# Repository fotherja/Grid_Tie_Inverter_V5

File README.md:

# Grid_Tie_Inverter_V5

Please refer to my site ( www.jamesfotherby.com ) where this project is being documented in detail

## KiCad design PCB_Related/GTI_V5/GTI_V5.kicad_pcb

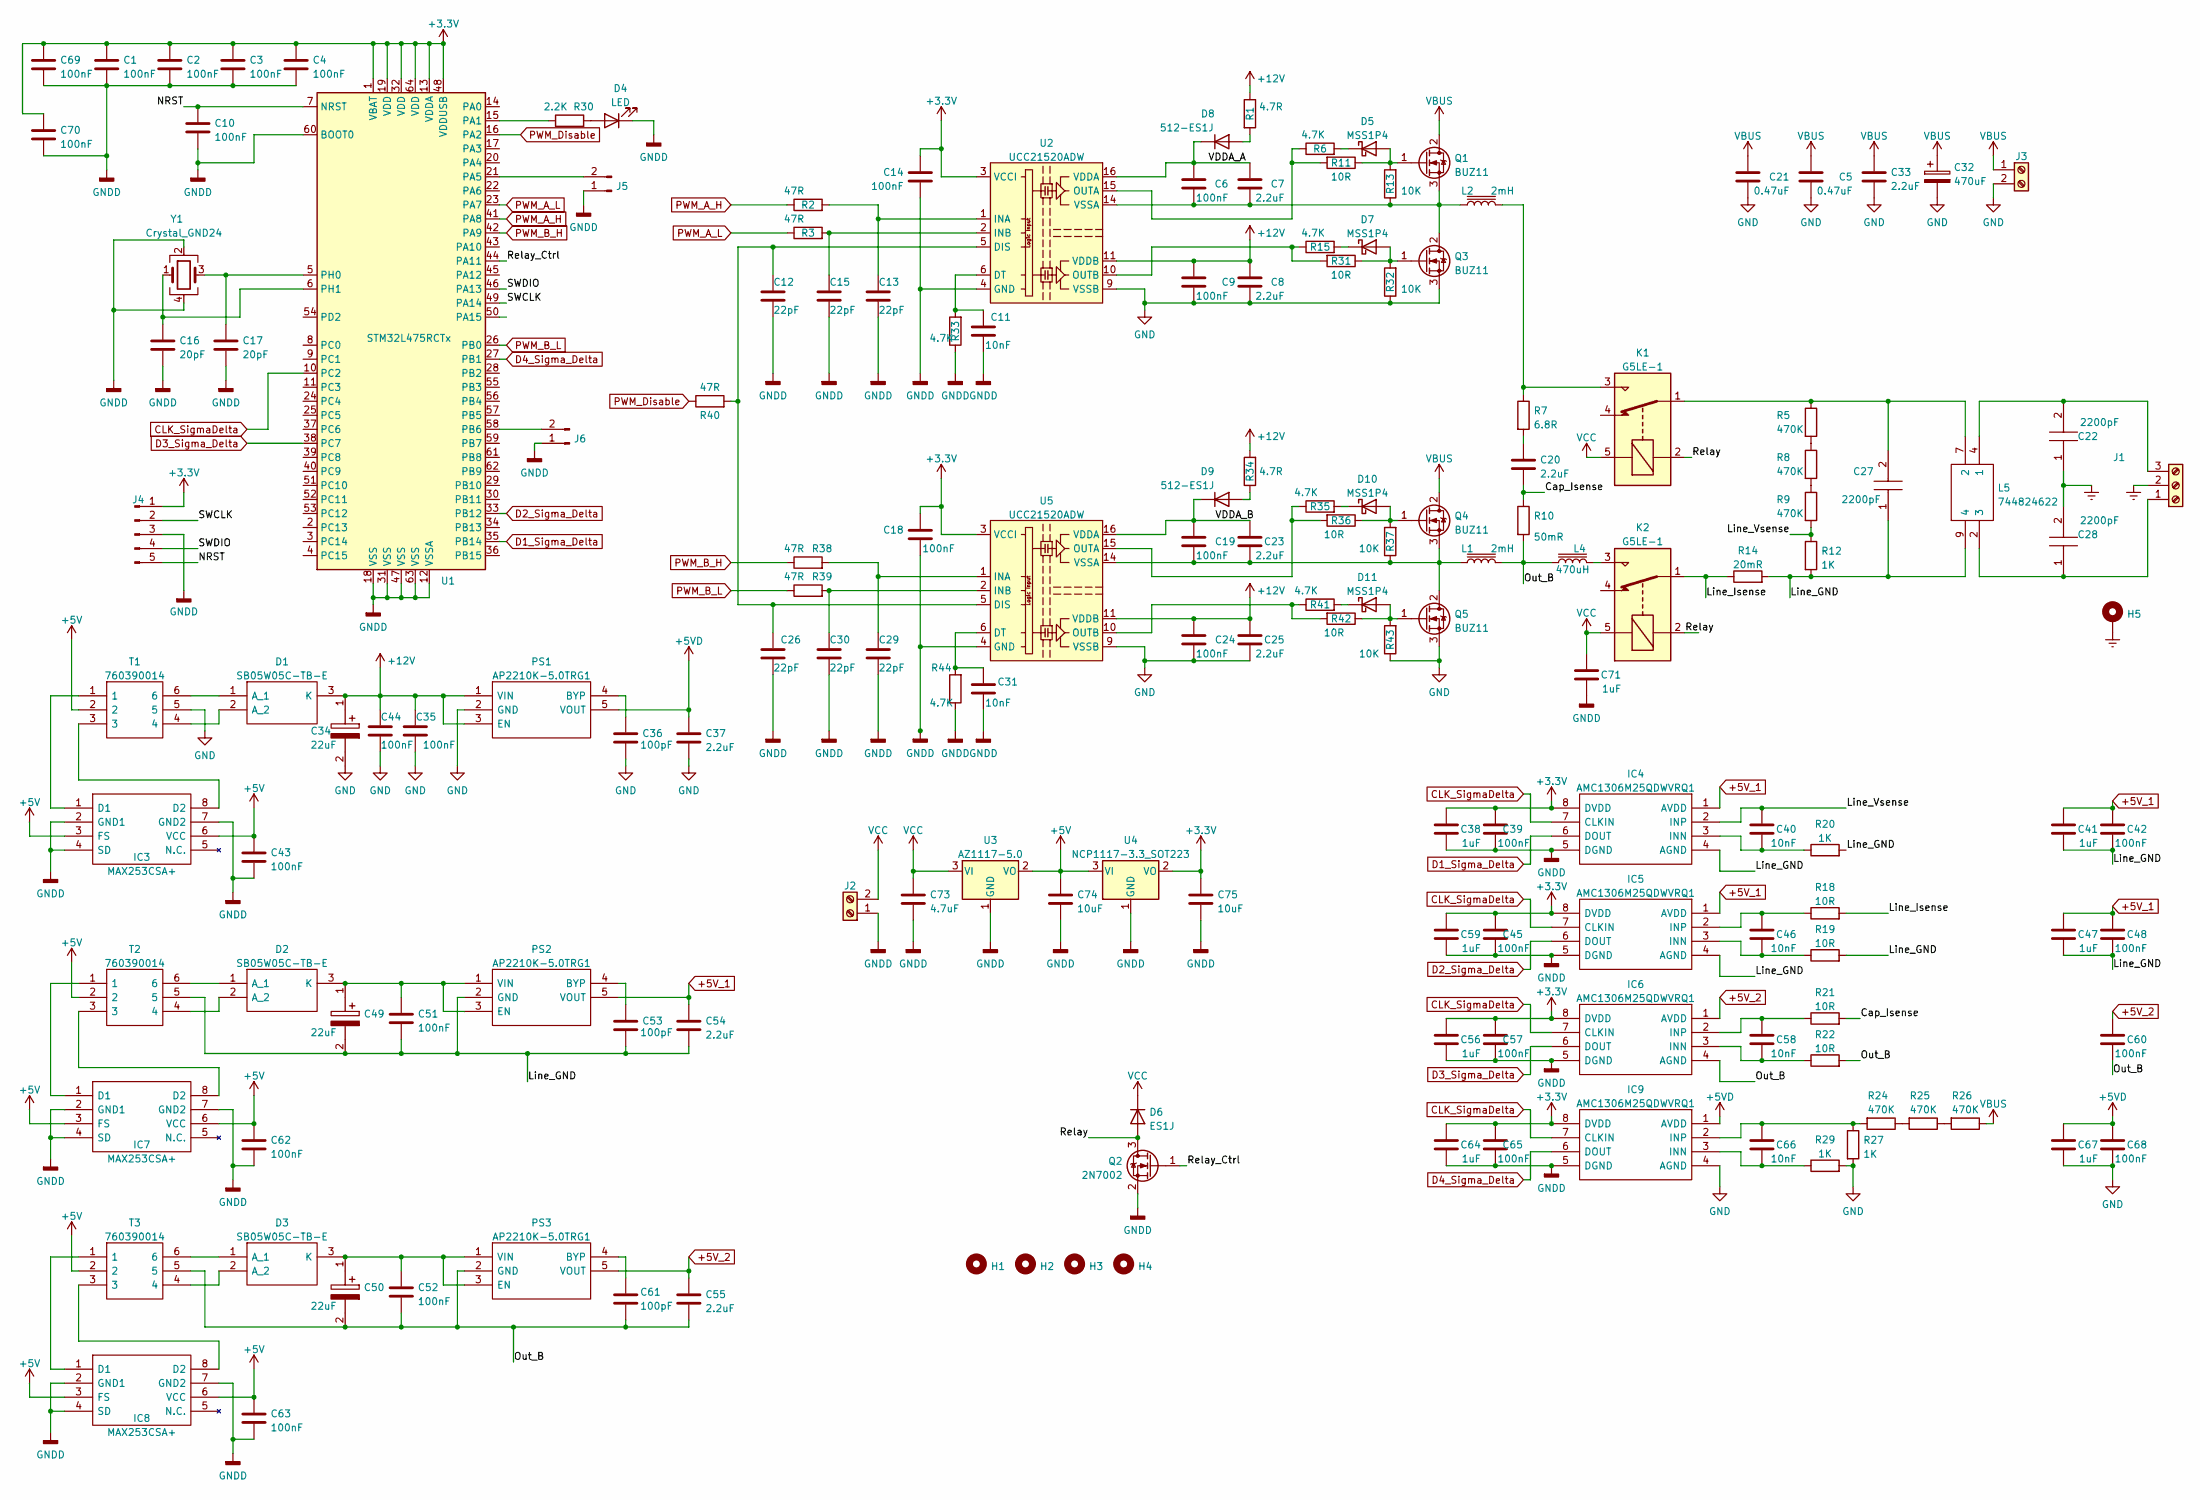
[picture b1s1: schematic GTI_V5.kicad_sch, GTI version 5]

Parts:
C1, C2, C3, C4, C6, C9, C10, C14, C18, C19, C24, C35, C39, C42, C43, C44, C45, C48, C51, C52, C57, C60, C62, C63, C65, C68, C69, C70: 100nF; C_0603_1608Metric
C5, C21: 0.47uF; C_2225_5664Metric
C7, C8, C23, C25, C37, C54, C55: 2.2uF; C_0603_1608Metric
C11, C31, C40, C46, C58, C66: 10nF; C_0603_1608Metric
C12, C13, C15, C26, C29, C30: 22pF; C_0603_1608Metric
C16, C17: 20pF; C_0603_1608Metric
C20: 2.2uF; C_Rect_L26.5mm_W11.5mm_P22.50mm_MKS4
C22, C27, C28: 2200pF; C901U222MZVDBA7317; Mouser Part Number 80-C901U222MZVDBAP
C32: 470uF; CP_Radial_D25.0mm_P10.00mm_SnapIn
C33: 2.2uF; C_Rect_L18.0mm_W11.0mm_P15.00mm_FKS3_FKP3
C34, C49, C50: 22uF; CAPPC3328X220N; Mouser Part Number 74-595D226X9020B2T
C36, C53, C61: 100pF; C_0603_1608Metric
C38, C41, C47, C56, C59, C64, C67, C71: 1uF; C_0603_1608Metric
C73: 4.7uF; C_0805_2012Metric
C74, C75: 10uF; C_0603_1608Metric
D1, D2, D3: SB05W05C-TB-E; SOT95P250X135-3N; Mouser Part Number 863-SB05W05C-TB-E
D4: LED; LED_0603_1608Metric
D5, D7, D10, D11: MSS1P4; D_MicroSMP
D6: ES1J; DIOM5227X250N
D8, D9: 512-ES1J; D_SMA
H1, H2, H3, H4: MountingHole; MountingHole_3.2mm_M3
H5: MountingHole_Pad; MountingHole_2.2mm_M2_Pad
IC3, IC7, IC8: MAX253CSA+; SOIC127P600X175-8N; Mouser Part Number 700-MAX253CSA
IC4, IC5, IC6, IC9: AMC1306M25QDWVRQ1; SOIC127P1150X280-8N; Mouser Part Number 595-MC1306M25QDWVRQ1
J1: Screw_Terminal_01x03; TerminalBlock_bornier-3_P5.08mm
J2, J3: Screw_Terminal_01x02; TerminalBlock_bornier-2_P5.08mm
J4: Conn_01x05_Male; PinHeader_1x05_P1.27mm_Vertical
J5, J6: Conn_01x02_Male; PinHeader_1x02_P1.27mm_Vertical
K1, K2: G5LE-1; Relay_SPDT_Omron-G5LE-1
L1, L2: 2mH; L_Toroid_Vertical_L35.1mm_W21.1mm_P18.50mm_Vishay_TJ6
L4: 470uH; L_Toroid_Vertical_L41.9mm_W19.1mm_P15.80mm_Vishay_TJ7
L5: 744824622; WE-CMB_L5; Mouser Part Number 710-744824622
PS1, PS2, PS3: AP2210K-5.0TRG1; SOT95P282X130-5N; Mouser Part Number 621-AP2210K-5.0TRG1
Q1, Q3, Q4, Q5: BUZ11; TO-220-3_Vertical
Q2: 2N7002; SOT-23
R1, R34: 4.7R; R_0603_1608Metric
R2, R3, R38, R39, R40: 47R; R_0603_1608Metric
R5, R8, R9, R24, R25, R26: 470K; R_0805_2012Metric
R6, R15, R33, R35, R41, R44: 4.7K; R_0603_1608Metric
R7: 6.8R; R_2512_6332Metric
R10: 50mR; R_2512_6332Metric
R11, R18, R19, R21, R22, R31, R36, R42: 10R; R_0603_1608Metric
R12, R20, R27, R29: 1K; R_0603_1608Metric
R13, R32, R37, R43: 10K; R_0603_1608Metric
R14: 20mR; R_2512_6332Metric
R30: 2.2K; R_0603_1608Metric
T1, T2, T3: 760390014; 760390015; Mouser Part Number 710-760390014
U1: STM32L475RCTx; LQFP-64_10x10mm_P0.5mm
U2, U5: UCC21520ADW; SOIC-16W_7.5x10.3mm_P1.27mm
U3: AZ1117-5.0; AZ1117CD50TRG1
U4: NCP1117-3.3_SOT223; SOT-223-3_TabPin2
Y1: Crystal_GND24; Crystal_SMD_Abracon_ABM10-4Pin_2.5x2.0mm

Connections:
+3.3V: C1.1, C2.1, C3.1, C4.1, C14.2, C18.2, C38.1, C39.1, C45.1, C56.1, C57.1, C59.1, C64.1, C65.1, C69.1, C70.1, C75.1, IC4.8 (DVDD), IC5.8 (DVDD), IC6.8 (DVDD), IC9.8 (DVDD), J4.1, U1.1 (VBAT), U1.13 (VDDA), U1.19 (VDD), U1.32 (VDD), U1.48 (VDDUSB), U1.64 (VDD), U2.3 (VCCI), U2.8 (VCCI), U4.2 (VO), U5.3 (VCCI), U5.8 (VCCI)
+5V: C43.1, C62.1, C63.1, C74.1, IC3.3 (FS), IC3.6 (VCC), IC7.3 (FS), IC7.6 (VCC), IC8.3 (FS), IC8.6 (VCC), T1.2, T2.2, T3.2, U3.2 (VO), U4.3 (VI)
+5VD: C37.1, C67.1, C68.1, IC9.1 (AVDD), PS1.5 (VOUT)
+5V_1: C41.1, C42.1, C47.1, C48.1, C54.1, IC4.1 (AVDD), IC5.1 (AVDD), PS2.5 (VOUT)
+5V_2: C55.1, C60.1, IC6.1 (AVDD), PS3.5 (VOUT)
+12V: C8.1, C9.2, C24.2, C25.1, C34.1, C35.1, C44.1, D1.3 (K), PS1.1 (VIN), PS1.3 (EN), R1.1, R34.2, U2.11 (VDDB), U5.11 (VDDB)
/Cap_Isense: C20.2, R10.1, R21.2
/Line_GND: C27.1, C41.2, C42.2, C47.2, C48.2, C49.2, C51.2, C53.2, C54.2, IC4.4 (AGND), IC5.4 (AGND), L5.9 (4), PS2.2 (GND), R12.2, R14.2, R19.2, R20.2, T2.5
/Line_Isense: K2.1, R14.1, R18.2
/Line_Vsense: C40.1, IC4.2 (INP), R9.2, R12.1
/NRST: C10.1, J4.5, U1.7 (NRST)
/Out_B: C50.2, C52.2, C55.2, C60.2, C61.2, IC6.4 (AGND), L1.2, L4.1, PS3.2 (GND), R10.2, R22.2, T3.5
/Relay: D6.1 (A), K1.2, K2.2, Q2.3 (D)
/Relay_Ctrl: Q2.1 (G), U1.44 (PA11)
/SWCLK: J4.2, U1.49 (PA14)
/SWDIO: J4.4, U1.46 (PA13)
/VDDA_A: C6.1, C7.1, D8.1 (K), U2.16 (VDDA)
/VDDA_B: C19.2, C23.1, D9.1 (K), U5.16 (VDDA)
CLK_SigmaDelta: IC4.7 (CLKIN), IC5.7 (CLKIN), IC6.7 (CLKIN), IC9.7 (CLKIN), U1.10 (PC2)
D1_Sigma_Delta: IC4.6 (DOUT), U1.35 (PB14)
D2_Sigma_Delta: IC5.6 (DOUT), U1.33 (PB12)
D3_Sigma_Delta: IC6.6 (DOUT), U1.38 (PC7)
D4_Sigma_Delta: IC9.6 (DOUT), U1.27 (PB1)
Earth: C22.1, C28.2, H5.1, J1.2
GND: C5.2, C8.2, C9.1, C21.2, C24.1, C25.2, C32.2, C33.2, C34.2, C35.2, C36.2, C37.2, C44.2, C67.2, C68.2, IC9.4 (AGND), J3.2, PS1.2 (GND), Q3.3 (S), Q5.3 (S), R27.2, R29.2, R32.1, R43.1, T1.5, U2.9 (VSSB), U5.9 (VSSB)
GNDD: C1.2, C2.2, C3.2, C4.2, C10.2, C11.1, C12.2, C13.2, C14.1, C15.2, C16.2, C17.2, C18.1, C26.2, C29.2, C30.2, C31.1, C38.2, C39.2, C43.2, C45.2, C56.2, C57.2, C59.2, C62.2, C63.2, C64.2, C65.2, C69.2, C70.2, C71.2, C73.2, C74.2, C75.2, D4.1 (K), IC3.2 (GND1), IC3.4 (SD), IC3.7 (GND2), IC4.5 (DGND), IC5.5 (DGND), IC6.5 (DGND), IC7.2 (GND1), IC7.4 (SD), IC7.7 (GND2), IC8.2 (GND1), IC8.4 (SD), IC8.7 (GND2), IC9.5 (DGND), J2.1, J4.3, J5.1, J6.1, Q2.2 (S), R33.1, R44.1, U1.12 (VSSA), U1.18 (VSS), U1.31 (VSS), U1.47 (VSS), U1.60 (BOOT0), U1.63 (VSS), U2.4 (GND), U3.1 (GND), U4.1 (GND), U5.4 (GND), Y1.2, Y1.4
unnamed: C6.2, C7.2, L2.1, Q1.3 (S), Q3.2 (D), R13.1, U2.14 (VSSA)
unnamed: C11.2, R33.2, U2.6 (DT)
unnamed: C12.1, C26.1, R40.2, U2.5 (DIS), U5.5 (DIS)
unnamed: C13.1, R2.2, U2.1 (INA)
unnamed: C15.1, R3.2, U2.2 (INB)
unnamed: C16.1, U1.6 (PH1), Y1.1
unnamed: C17.1, U1.5 (PH0), Y1.3
unnamed: C19.1, C23.2, L1.1, Q4.3 (S), Q5.2 (D), R37.1, U5.14 (VSSA)
unnamed: C20.1, R7.2
unnamed: C22.2, J1.3, L5.4 (1)
unnamed: C27.2, K1.1, L5.7 (2), R5.1
unnamed: C28.1, J1.1, L5.2 (3)
unnamed: C29.1, R38.2, U5.1 (INA)
unnamed: C30.1, R39.2, U5.2 (INB)
unnamed: C31.2, R44.2, U5.6 (DT)
unnamed: C36.1, PS1.4 (BYP)
unnamed: C40.2, IC4.3 (INN), R20.1
unnamed: C46.1, IC5.2 (INP), R18.1
unnamed: C46.2, IC5.3 (INN), R19.1
unnamed: C49.1, C51.1, D2.3 (K), PS2.1 (VIN), PS2.3 (EN)
unnamed: C50.1, C52.1, D3.3 (K), PS3.1 (VIN), PS3.3 (EN)
unnamed: C53.1, PS2.4 (BYP)
unnamed: C58.1, IC6.2 (INP), R21.1
unnamed: C58.2, IC6.3 (INN), R22.1
unnamed: C61.1, PS3.4 (BYP)
unnamed: C66.1, IC9.2 (INP), R24.2, R27.1
unnamed: C66.2, IC9.3 (INN), R29.1
unnamed: D1.1 (A_1), T1.6
unnamed: D1.2 (A_2), T1.4
unnamed: D2.1 (A_1), T2.6
unnamed: D2.2 (A_2), T2.4
unnamed: D3.1 (A_1), T3.6
unnamed: D3.2 (A_2), T3.4
unnamed: D4.2 (A), R30.2
unnamed: D5.1 (K), R6.2
unnamed: D5.2 (A), Q1.1 (G), R11.1, R13.2
unnamed: D7.1 (K), R15.2
unnamed: D7.2 (A), Q3.1 (G), R31.1, R32.2
unnamed: D8.2 (A), R1.2
unnamed: D9.2 (A), R34.1
unnamed: D10.1 (K), R35.2
unnamed: D10.2 (A), Q4.1 (G), R36.1, R37.2
unnamed: D11.1 (K), R41.2
unnamed: D11.2 (A), Q5.1 (G), R42.1, R43.2
unnamed: IC3.1 (D1), T1.1
unnamed: IC3.8 (D2), T1.3
unnamed: IC7.1 (D1), T2.1
unnamed: IC7.8 (D2), T2.3
unnamed: IC8.1 (D1), T3.1
unnamed: IC8.8 (D2), T3.3
unnamed: J5.2, U1.21 (PA5)
unnamed: J6.2, U1.58 (PB6)
unnamed: K1.3, L2.2, R7.1
unnamed: K2.3, L4.2
unnamed: R5.2, R8.1
unnamed: R8.2, R9.1
unnamed: R6.1, R11.2, U2.15 (OUTA)
unnamed: R15.1, R31.2, U2.10 (OUTB)
unnamed: R24.1, R25.2
unnamed: R25.1, R26.2
unnamed: R30.1, U1.15 (PA1)
unnamed: R35.1, R36.2, U5.15 (OUTA)
unnamed: R41.1, R42.2, U5.10 (OUTB)
PWM_A_H: R2.1, U1.41 (PA8)
PWM_A_L: R3.1, U1.23 (PA7)
PWM_B_H: R38.1, U1.42 (PA9)
PWM_B_L: R39.1, U1.26 (PB0)
PWM_Disable: R40.1, U1.16 (PA2)
VBUS: C5.1, C21.1, C32.1, C33.1, J3.1, Q1.2 (D), Q4.2 (D), R26.1
VCC: C71.1, C73.1, D6.2 (K), J2.2, K1.5, K2.5, U3.3 (VI)

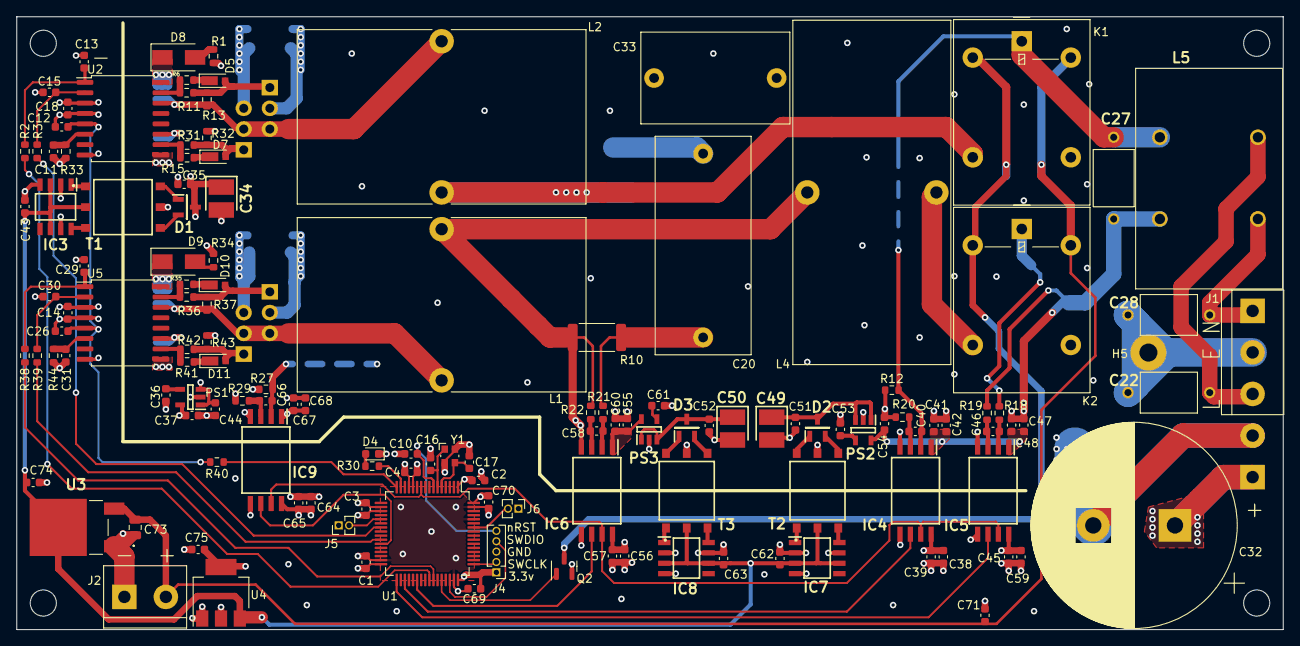
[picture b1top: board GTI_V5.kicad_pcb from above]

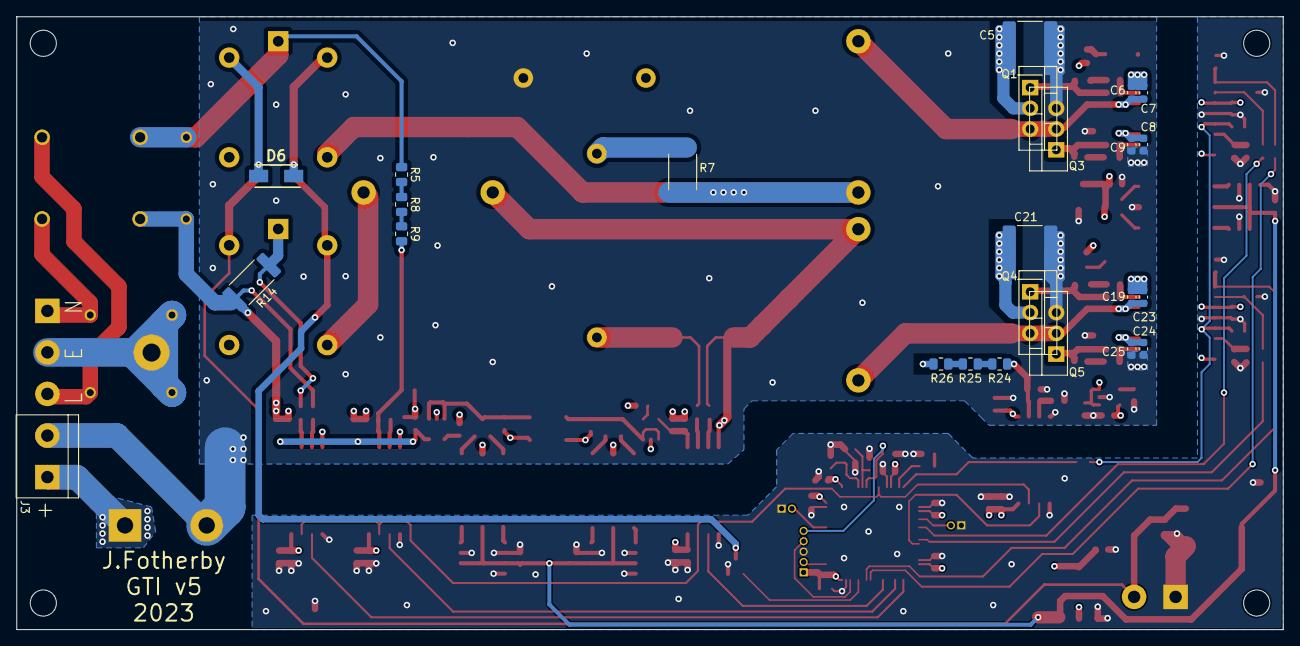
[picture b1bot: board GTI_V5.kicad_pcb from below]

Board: 4 copper layers, 155.0 x 75.0 mm, 165 parts (24 on the bottom side), 96 nets.

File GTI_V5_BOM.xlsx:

Ref | Qnty | Value | Cmp name | Footprint | Description | Manufacture Part number |  | Link
C1, C2, C3, C4, C6, C9, C10, C14, C18, C19, C24, C35, C39, C42, C43, C44, C45, 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 | 28 | 100nF | C | Capacitor_SMD:C_0603_1608Metric | Unpolarized capacitor
C5, C21, | 2 | 0.47uF | C | Capacitor_SMD:C_2225_5664Metric | Unpolarized capacitor
C7, C8, C23, C25, C37, C54, C55, | 7 | 2.2uF | C | Capacitor_SMD:C_0603_1608Metric | Unpolarized capacitor
C11, C31, C40, C46, C58, C66, | 6 | 10nF | C | Capacitor_SMD:C_0603_1608Metric | Unpolarized capacitor
C12, C13, C15, C26, C29, C30, | 6 | 22pF | C | Capacitor_SMD:C_0603_1608Metric | Unpolarized capacitor
C16, C17, | 2 | 20pF | C | Capacitor_SMD:C_0603_1608Metric | Unpolarized capacitor
C20, | 1 | 2.2uF | C | Capacitor_THT:C_Rect_L26.5mm_W11.5mm_P22.50mm_MKS4 | Unpolarized capacitor | Film Capacitors 2.2uF 520VDC 10% Rad, 250VAC |  | https://www.mouser.co.uk/ProductDetail/80-R71VN42204030K
C22, C27, C28, | 3 | 2200pF | C901U222MZVDBA7317 | C901U222MZVDBA7317:C901U222MZVDBA7317 | C900AC SFTY X1-440 Y2-300, Ceramic, 2200 pF, 20%, 440 VAC, 440 VAC (X1), 300 VA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
C32, | 1 | 470uF | C_Polarized | Capacitor_THT:CP_Radial_D25.0mm_P10.00mm_SnapIn | Polarized capacitor | Aluminium Electrolytic Capacitors - Snap In 450V 470uF 20% 9K Hours |  | https://www.digikey.co.uk/en/products/detail/united-chemi-co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
C33, | 1 | 2.2uF | C | Capacitor_THT:C_Rect_L18.0mm_W11.0mm_P15.00mm_FKS3_FKP3 | Unpolarized capacitor | Film Capacitors 450V 2.2uF |  | https://www.mouser.co.uk/ProductDetail/80-R71XI422050H0K
C34, C49, C50, | 3 | 22uF | 595D226X9020B2T | 595D226X9020:CAPPC3328X220N | Solid Tantalum Chip Capacitors TANTAMOUNT(TM), Conformal Coated, Maximum CV |  |  | https://www.mouser.co.uk/ProductDetail/74-595D226X9020B2T
C36, C53, C61, | 3 | 100pF | C | Capacitor_SMD:C_0603_1608Metric | Unpolarized capacitor
C38, C41, C47, C56, C59, C64, C67, C71, | 8 | 1uF | C | Capacitor_SMD:C_0603_1608Metric | Unpolarized capacitor
C73, | 1 | 10uF | C | Capacitor_SMD:C_0805_2012Metric | Unpolarized capacitor
C74, C75, | 2 | 10uF | C | Capacitor_SMD:C_0603_1608Metric | Unpolarized capacitor
D1, D2, D3, | 3 | SB05W05C-TB-E | SB05W05C-TB-E | SB05W05C:SOT95P250X135-3N | Dual SMT Schottky Diode Common Cathode |  |  | https://www.mouser.co.uk/ProductDetail/863-SB05W05C-TB-E
D4, | 1 | LED | LED | LED_SMD:LED_0603_1608Metric | Light emitting diode
D5, D7, D10, D11, | 4 | MSS1P4 | B120-E3 | Diode_SMD:D_MicroSMP | 20V 1A Schottky Barrier Rectifier Diode, SMA(DO-214AC) |  |  | https://www.mouser.co.uk/ProductDetail/Vishay-General-Semico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
D6, | 1 | DIODE | DIODE | ES1J:DIOM5227X250N | Diode, anode on pin 1, for simulation only!
D8, D9, | 2 | 512-ES1J | MRA4005T3G | Diode_SMD:D_SMA | 600V, 1A, General Purpose Rectifier Diode, SMA(DO-214AC) |  |  | https://www.mouser.co.uk/ProductDetail/onsemi-Fairchild/ES1J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
H1, H2, H3, H4, | 4 | MountingHole | MountingHole | MountingHole:MountingHole_3.2mm_M3 | Mounting Hole without connection
H5, | 1 | MountingHole_Pad | MountingHole_Pad | MountingHole:MountingHole_2.2mm_M2_Pad | Mounting Hole with connection
IC3, IC7, IC8, | 3 | MAX253CSA+ | MAX253CSA+ | MAX253CSA:SOIC127P600X175-8N | MAX253CSA+, General Purpose Driver, 8-Pin, SOIC N |  |  | https://www.mouser.co.uk/ProductDetail/700-MAX253CSA
IC4, IC5, IC6, IC9, | 4 | AMC1306M25QDWVRQ1 | AMC1306M25QDWVRQ1 | AMC1306:SOIC127P1150X280-8N | Data Acquisition ADCs/DACs - Specialized Automotive, +/-250-mV input, precision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 |  |  | https://www.mouser.co.uk/ProductDetail/595-MC1306M25QDWVRQ1
J1, | 1 | Screw_Terminal_01x03 | Screw_Terminal_01x03 | TerminalBlock:TerminalBlock_bornier-3_P5.08mm | Generic screw terminal, single row, 01x03, script generated (kicad-library-util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
J2, J3, | 2 | Screw_Terminal_01x02 | Screw_Terminal_01x02 | TerminalBlock:TerminalBlock_bornier-2_P5.08mm | Generic screw terminal, single row, 01x02, script generated (kicad-library-util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
J4, | 1 | Conn_01x05_Male | Conn_01x05_Male | Connector_PinHeader_1.27mm:PinHeader_1x05_P1.27mm_Vertical | Generic connector, single row, 01x05, script generated (kicad-library-utils/sch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
J5, J6, | 2 | Conn_01x02_Male | Conn_01x02_Male | Connector_PinHeader_1.27mm:PinHeader_1x02_P1.27mm_Vertical | Generic connector, single row, 01x02, script generated (kicad-library-utils/sch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
K1, K2, | 2 | G5LE-1 | G5LE-1 | Relay_THT:Relay_SPDT_Omron-G5LE-1 | Omron G5LE relay, Miniature Single Pole, SPDT, 10A |  |  | https://www.mouser.co.uk/ProductDetail/653-G5LE-1-VDDC12
L1, L2, | 2 | 2mH | L_Iron | Inductor_THT:L_Toroid_Vertical_L35.1mm_W21.1mm_P18.50mm_Vishay_TJ6 | Inductor with iron core |  |  | https://powermagneticsstore.co.uk/shop/fs-185090-2.html
L4, | 1 | 1mH | L_Iron | Inductor_THT:L_Toroid_Vertical_L41.9mm_W19.1mm_P15.80mm_Vishay_TJ7 | Inductor with iron core |  |  | https://powermagneticsstore.co.uk/shop/fs-185090-2.html
L5, | 1 | 744824622 | 744824622 | 744824622:WE-CMB_L5 | Current Compensated Choke WE-CMB | Common Mode Chokes / Filters WE-CMB Choke Type L 2.2mH 6A 20mOhm |  | https://www.mouser.co.uk/ProductDetail/710-744824622
PS1, PS2, PS3, | 3 | AP2210K-5.0TRG1 | AP2210K-5.0TRG1 | AP2210K-5.0TRG1:SOT95P282X130-5N | LDO Voltage Regulators 300mA CMOS LDO 5.0V 250mV |  |  | https://www.mouser.co.uk/ProductDetail/621-AP2210K-5.0TRG1
Q1, Q3, Q4, Q5, | 4 | BUZ11 | BUZ11 | Package_TO_SOT_THT:TO-220-3_Vertical | 30A Id, 50V Vds, N-Channel Power MOSFET, TO-220 |  |  | https://www.st.com/resource/en/datasheet/stp16nf06.pdf
Q2, | 1 | 2N7002 | 2N7002 | Package_TO_SOT_SMD:SOT-23 | 0.115A Id, 60V Vds, N-Channel MOSFET, SOT-23
R1, R34, | 2 | 4.7R | R | Resistor_SMD:R_0603_1608Metric | Resistor
R2, R3, R38, R39, R40, | 5 | 47R | R | Resistor_SMD:R_0603_1608Metric | Resistor
R12, R20, R27, R29, R33, R44, | 6 | 1K | R | Resistor_SMD:R_0603_1608Metric | Resistor
R5, R8, R9, R24, R25, R26, | 6 | 470K | R | Resistor_SMD:R_0805_2012Metric | Resistor
R6, R15, R35, R41, | 4 | 2.2R | R | Resistor_SMD:R_0603_1608Metric | Resistor
R7, | 1 | 6.8R | R | Resistor_SMD:R_2512_6332Metric | Resistor
R10, | 1 | 50mR | R | Resistor_SMD:R_2512_6332Metric | Resistor
R11, R18, R19, R21, R22, R31, R36, R42, | 8 | 10R | R | Resistor_SMD:R_0603_1608Metric | Resistor
R13, R32, R37, R43, | 4 | 10K | R | Resistor_SMD:R_0603_1608Metric | Resistor
R14, | 1 | 20mR | R | Resistor_SMD:R_2512_6332Metric | Resistor
R30, | 1 | 4.7K | R | Resistor_SMD:R_0603_1608Metric | Resistor
T1, | 1 | 750316770 | 750316770 |  | Power Transformers 1W Push Pull TOR4.3/2.8/2.3 | 5 to 12V |  | https://www.mouser.co.uk/ProductDetail/710-750316770
T2, T3, | 2 | 760390014 | 760390014 | 760390014:760390015 | Audio Transformers / Signal Transformers MID-SN6501 TI Driver Toroid .475mH 5VDC | 5 to 5V |  | https://www.mouser.co.uk/ProductDetail/710-760390014
U1, | 1 | STM32L475RCTx | STM32L475RCTx | Package_QFP:LQFP-64_10x10mm_P0.5mm | ARM Cortex-M4 MCU, 256KB flash, 128KB RAM, 80MHz, 1.71-3.6V, 51 GPIO, LQFP-64 | STM32L475RCT3 |  | https://www.mouser.co.uk/ProductDetail/511-STM32L475RCT3
U2, U5, | 2 | UCC21520ADW | UCC21520ADW | Package_SO:SOIC-16W_7.5x10.3mm_P1.27mm | Isolated Dual-Channel Gate Driver, Output Current 4.0/6.0A, 5.7kV Isolation, 5V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
U3, | 1 | AZ1117-5.0 | AZ1117-5.0 | AZ1117CD-5.0TRG1:AZ1117CD50TRG1 | 1A 20V Fixed LDO Linear Regulator, 5.0V, SOT-89/SOT-223/TO-220/TO-252/TO-263 |  |  | https://www.mouser.co.uk/ProductDetail/Diodes-Incorporated/A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
U4, | 1 | TC2117-3.3VDBTR | TC2117-3.3VDBTR | Package_TO_SOT_SMD:SOT-223-3_TabPin2 | 1A Low drop-out regulator, Fixed Output 3.3V, SOT-223 |  |  | https://www.mouser.co.uk/ProductDetail/Microchip-Technology/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
Y1, | 1 | Crystal_GND24 | Crystal_GND24 | Crystal:Crystal_SMD_Abracon_ABM10-4Pin_2.5x2.0mm | Four pin crystal, GND on pins 2 and 4 | ABM10-16.000MHZ-D30-T3 |  | https://www.mouser.co.uk/ProductDetail/ABRACON/ABM10-16.000M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

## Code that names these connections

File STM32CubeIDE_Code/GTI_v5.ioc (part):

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Mcu.Name=STM32L475R(C-E-G)Tx
Mcu.Package=LQFP64
Mcu.UserName=STM32L475RCTx
PA1.GPIOParameters=GPIO_Speed,GPIO_Label
PA1.GPIO_Label=LED
PA1.GPIO_Speed=GPIO_SPEED_FREQ_MEDIUM
PA1.Signal=GPIO_Output
PA11.GPIOParameters=GPIO_Speed,GPIO_Label
PA11.GPIO_Label=Relay
PA11.GPIO_Speed=GPIO_SPEED_FREQ_MEDIUM
PA11.Signal=GPIO_Output
PA2.GPIOParameters=GPIO_Speed,PinState,GPIO_Label
PA2.GPIO_Label=Driver_Disable
PA2.GPIO_Speed=GPIO_SPEED_FREQ_MEDIUM
PA2.PinState=GPIO_PIN_SET
PA2.Signal=GPIO_Output
PA5.GPIOParameters=GPIO_Label
PA5.GPIO_Label=DAC_Out
PA5.Signal=COMP_DAC12_group
PA7.GPIOParameters=GPIO_Speed,GPIO_Label
PA7.GPIO_Label=PWM_A_L
PA7.GPIO_Speed=GPIO_SPEED_FREQ_VERY_HIGH
PA7.Mode=PWM Generation1 CH1 CH1N
PA7.Signal=TIM1_CH1N
PA8.GPIOParameters=GPIO_Speed,GPIO_Label
PA8.GPIO_Label=PWM_A_H
PA8.GPIO_Speed=GPIO_SPEED_FREQ_VERY_HIGH
PA8.Signal=S_TIM1_CH1
PA9.GPIOParameters=GPIO_Speed,GPIO_Label
PA9.GPIO_Label=PWM_B_H
PA9.GPIO_Speed=GPIO_SPEED_FREQ_VERY_HIGH
PA9.Signal=S_TIM1_CH2
PB0.GPIOParameters=GPIO_Speed,GPIO_Label
PB0.GPIO_Label=PWM_B_L
PB0.GPIO_Speed=GPIO_SPEED_FREQ_VERY_HIGH
PB0.Mode=PWM Generation2 CH2 CH2N
PB0.Signal=TIM1_CH2N
PB1.GPIOParameters=GPIO_Speed,GPIO_Label
PB1.GPIO_Label=Vbus_DIN
PB1.GPIO_Speed=GPIO_SPEED_FREQ_VERY_HIGH
PB1.Signal=S_DATAIN0DFSDM1
PB12.GPIOParameters=GPIO_Speed,GPIO_Label
PB12.GPIO_Label=Igrid_DIN
PB12.GPIO_Speed=GPIO_SPEED_FREQ_VERY_HIGH
PB12.Signal=S_DATAIN1DFSDM1
PB14.GPIOParameters=GPIO_Speed,GPIO_Label
PB14.GPIO_Label=Vgrid_DIN
PB14.GPIO_Speed=GPIO_SPEED_FREQ_VERY_HIGH
PB14.Signal=S_DATAIN2DFSDM1
PC2.GPIOParameters=GPIO_Speed,GPIO_Label
PC2.GPIO_Label=DFSDM_Clk
PC2.GPIO_Speed=GPIO_SPEED_FREQ_VERY_HIGH
PC2.Signal=S_CKOUTDFSDM1
PC7.GPIOParameters=GPIO_Speed,GPIO_Label
PC7.GPIO_Label=Icap_DIN
PC7.GPIO_Speed=GPIO_SPEED_FREQ_VERY_HIGH
PC7.Signal=S_DATAIN3DFSDM1
PH0-OSC_IN\ (PH0).Mode=HSE-External-Oscillator
PH0-OSC_IN\ (PH0).Signal=RCC_OSC_IN
PH1-OSC_OUT\ (PH1).Mode=HSE-External-Oscillator
PH1-OSC_OUT\ (PH1).Signal=RCC_OSC_OUT
RCC.HSE_VALUE=16000000
RCC.SYSCLKFreq_VALUE=80000000
RCC.SYSCLKSource=RCC_SYSCLKSOURCE_PLLCLK
board=custom

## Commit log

2023-03-16 Hardware
    The PCB has been designed and sent for manufacturing
2023-03-29 PCB now assembled - with these component values
    The hardware deadtime resistors on the UCC21520 are 4.7K for a 47ns deadtime. This can always be increased further in software on the STM32L475
2023-03-29 updated schematic inductor values that I'm using
2023-03-29 Added BOM to repo
2023-03-29 Added Schematic PDF
2023-03-31 First code upload
    This code performs most of the necessary functions including:
    - Outputting PWM
    - Implementing a PLL
    - Performing safety checks and overcurrent/voltage protection using the analog watchdog on the DFSDM peripheral
    - Implementing a PR (proportional resonant) controller
    Plenty still to do:
2023-03-31 Successful grid tie
    Successfully grid tied and output 40W through a 12V transformer (waiting for a TVS prior to going to higher voltages)
    We have the PR working with a 150Hz compensator - will be easy to add more (250 and 350Hz compensators)
    Next I won't to implement a CPU monitor to see how much processing power we have left (plenty I hope, although HAL is so inefficient)
2023-04-04 100W Grid Tie
2023-06-14 600W Transformerless GT
2023-06-25 600W Grid Tied
    Working brilliantly. We employ:
    - PI control + Resonant controller + Harmonic compensators
    - Feedforward control
    - With have a PI loop which adjusts our output current to pull the bus voltage to 370 Volts
2023-06-27 Add files via upload
    corrected schematic gate drive resistor symbols (4.7K to 4.7R)
